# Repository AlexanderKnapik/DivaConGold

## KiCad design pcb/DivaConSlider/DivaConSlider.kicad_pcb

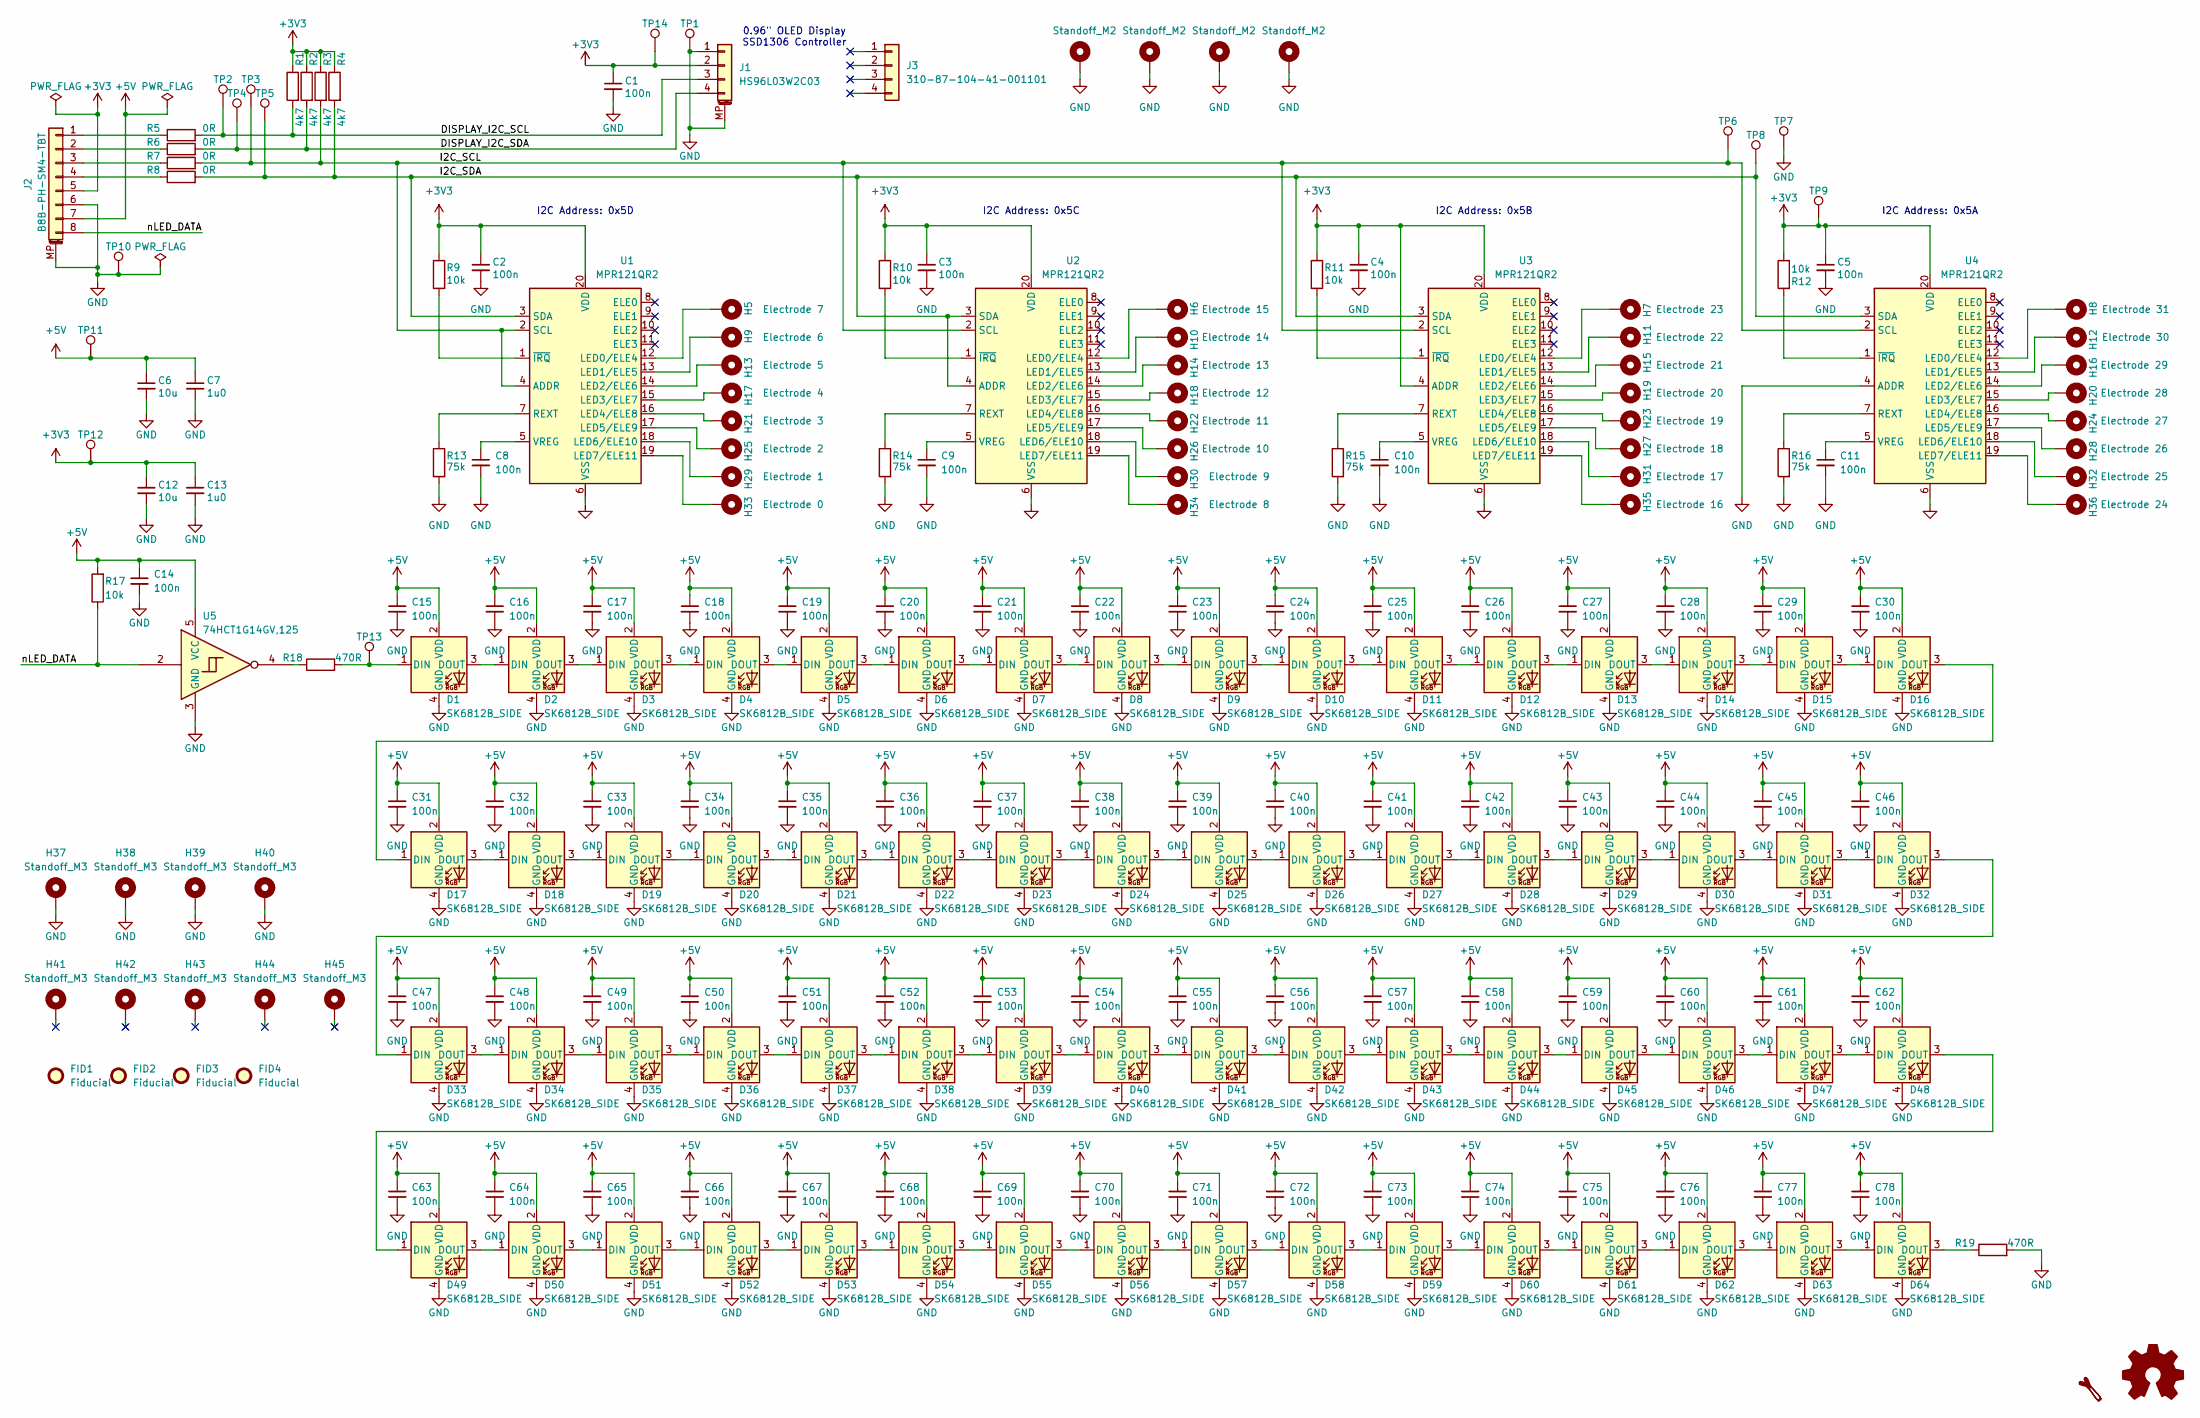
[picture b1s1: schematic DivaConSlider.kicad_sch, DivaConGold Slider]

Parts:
C1, C2, C3, C4, C5, C8, C9, C10, C11, C14, C15, C16, C17, C18, C19, C20, C21, C22, C23, C24, C25, C26, C27, C28, C29, C30, C31, C32, C33, C34, C35, C36, C37, C38, C39, C40, C41, C42, C43, C44, C45, C46, C47, C48, C49, C50, C51, C52, C53, C54, C55, C56, C57, C58, C59, C60, C61, C62, C63, C64, C65, C66, C67, C68, C69, C70, C71, C72, C73, C74, C75, C76, C77, C78: 100n; C_0603_1608Metric; Voltage 50V; PartNumber CL10B104KB8NNNC
C6, C12: 10u; C_0805_2012Metric; Voltage 16V; PartNumber CL21B106KOQNNNE
C7, C13: 1u0; C_0603_1608Metric; Voltage 16V; PartNumber CL10B105KO8NNNC
D1, D2, D3, D4, D5, D6, D7, D8, D9, D10, D11, D12, D13, D14, D15, D16, D17, D18, D19, D20, D21, D22, D23, D24, D25, D26, D27, D28, D29, D30, D31, D32, D33, D34, D35, D36, D37, D38, D39, D40, D41, D42, D43, D44, D45, D46, D47, D48, D49, D50, D51, D52, D53, D54, D55, D56, D57, D58, D59, D60, D61, D62, D63, D64: SK6812B_SIDE; LED_SK6812B_SIDE; PartNumber SK6812SIDE-A
FID1, FID2, FID3, FID4: Fiducial; Fiducial_0.5mm_Mask1.5mm
H1, H2, H3, H4: Standoff_M2; MountingHole_2.2mm_M2_Pad
H5: Electrode 7; Touchpad_15mmx42mm
H6: Electrode 15; Touchpad_15mmx42mm
H7: Electrode 23; Touchpad_15mmx42mm
H8: Electrode 31; Touchpad_15mmx42mm
H9: Electrode 6; Touchpad_15mmx42mm
H10: Electrode 14; Touchpad_15mmx42mm
H11: Electrode 22; Touchpad_15mmx42mm
H12: Electrode 30; Touchpad_15mmx42mm
H13: Electrode 5; Touchpad_15mmx42mm
H14: Electrode 13; Touchpad_15mmx42mm
H15: Electrode 21; Touchpad_15mmx42mm
H16: Electrode 29; Touchpad_15mmx42mm
H17: Electrode 4; Touchpad_15mmx42mm
H18: Electrode 12; Touchpad_15mmx42mm
H19: Electrode 20; Touchpad_15mmx42mm
H20: Electrode 28; Touchpad_15mmx42mm
H21: Electrode 3; Touchpad_15mmx42mm
H22: Electrode 11; Touchpad_15mmx42mm
H23: Electrode 19; Touchpad_15mmx42mm
H24: Electrode 27; Touchpad_15mmx42mm
H25: Electrode 2; Touchpad_15mmx42mm
H26: Electrode 10; Touchpad_15mmx42mm
H27: Electrode 18; Touchpad_15mmx42mm
H28: Electrode 26; Touchpad_15mmx42mm
H29: Electrode 1; Touchpad_15mmx42mm
H30: Electrode 9; Touchpad_15mmx42mm
H31: Electrode 17; Touchpad_15mmx42mm
H32: Electrode 25; Touchpad_15mmx42mm
H33: Electrode 0; Touchpad_15mmx42mm
H34: Electrode 8; Touchpad_15mmx42mm
H35: Electrode 16; Touchpad_15mmx42mm
H36: Electrode 24; Touchpad_15mmx42mm
H37, H38, H39, H40: Standoff_M3; MountingHole_3.2mm_M3_Pad_Via
H41, H42, H43, H44, H45: Standoff_M3; MountingHole_3.2mm_M3_Pad
J1: HS96L03W2C03; Hansheng_HS96L03W2C03; PartNumber HS96L03W2C03
J2: B8B-PH-SM4-TBT; JST_PH_B8B-PH-SM4-TB_1x08-1MP_P2.00mm_Vertical; PartNumber B8B-PH-SM4-TBT
J3: 310-87-104-41-001101; PinHeader_1x04_P2.54mm_Vertical; PartNumber 310-87-104-41-001101
R1, R2, R3, R4: 4k7; R_0603_1608Metric; PartNumber RMCF0603FT4K70
R5, R6, R7, R8: 0R; R_0603_1608Metric; PartNumber RMCF0603ZT0R00
R9, R10, R11, R12, R17: 10k; R_0603_1608Metric; PartNumber RMCF0603FT10K0
R13, R14, R15, R16: 75k; R_0603_1608Metric; PartNumber RMCF0603FT75K0
R18: 470R; R_0603_1608Metric; PartNumber RMCF0603FT470R
R19: 470R; R_0603_1608Metric
SYM1: Logo_Open_Hardware_Small; OSHW-Logo_5.7x6mm_SilkScreen
SYM2: Leek; Leek-Logo_6.3mm_Silkscreen
TP1, TP2, TP3, TP4, TP5, TP6, TP7, TP8, TP9, TP10, TP11, TP12, TP13, TP14: TestPoint; TestPoint_Pad_D1.5mm
U1, U2, U3, U4: MPR121QR2; UQFN-20_3x3mm_P0.4mm; PartNumber MPR121QR2
U5: 74HCT1G14GV,125; SC-74A-5_1.55x2.9mm_P0.95mm; PartNumber 74HCT1G14GV,125

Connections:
+3V3: C1.1, C2.1, C3.1, C4.1, C5.1, C12.1, C13.1, J1.2, J2.5, R1.1, R2.1, R3.1, R4.1, R9.1, R10.1, R11.1, R12.2, TP9.1, TP12.1, TP14.1, U1.20 (VDD), U2.20 (VDD), U3.4 (ADDR), U3.20 (VDD), U4.20 (VDD)
+5V: C6.1, C7.1, C14.1, C15.1, C16.1, C17.1, C18.1, C19.1, C20.1, C21.1, C22.1, C23.1, C24.1, C25.1, C26.1, C27.1, C28.1, C29.1, C30.1, C31.1, C32.1, C33.1, C34.1, C35.1, C36.1, C37.1, C38.1, C39.1, C40.1, C41.1, C42.1, C43.1, C44.1, C45.1, C46.1, C47.1, C48.1, C49.1, C50.1, C51.1, C52.1, C53.1, C54.1, C55.1, C56.1, C57.1, C58.1, C59.1, C60.1, C61.1, C62.1, C63.1, C64.1, C65.1, C66.1, C67.1, C68.1, C69.1, C70.1, C71.1, C72.1, C73.1, C74.1, C75.1, C76.1, C77.1, C78.1, D1.2 (VDD), D2.2 (VDD), D3.2 (VDD), D4.2 (VDD), D5.2 (VDD), D6.2 (VDD), D7.2 (VDD), D8.2 (VDD), D9.2 (VDD), D10.2 (VDD), D11.2 (VDD), D12.2 (VDD), D13.2 (VDD), D14.2 (VDD), D15.2 (VDD), D16.2 (VDD), D17.2 (VDD), D18.2 (VDD), D19.2 (VDD), D20.2 (VDD), D21.2 (VDD), D22.2 (VDD), D23.2 (VDD), D24.2 (VDD), D25.2 (VDD), D26.2 (VDD), D27.2 (VDD), D28.2 (VDD), D29.2 (VDD), D30.2 (VDD), D31.2 (VDD), D32.2 (VDD), D33.2 (VDD), D34.2 (VDD), D35.2 (VDD), D36.2 (VDD), D37.2 (VDD), D38.2 (VDD), D39.2 (VDD), D40.2 (VDD), D41.2 (VDD), D42.2 (VDD), D43.2 (VDD), D44.2 (VDD), D45.2 (VDD), D46.2 (VDD), D47.2 (VDD), D48.2 (VDD), D49.2 (VDD), D50.2 (VDD), D51.2 (VDD), D52.2 (VDD), D53.2 (VDD), D54.2 (VDD), D55.2 (VDD), D56.2 (VDD), D57.2 (VDD), D58.2 (VDD), D59.2 (VDD), D60.2 (VDD), D61.2 (VDD), D62.2 (VDD), D63.2 (VDD), D64.2 (VDD), J2.7, R17.2, TP11.1, U5.5 (VCC)
/DISPLAY_I2C_SCL: J1.3, R1.2, R5.2, TP2.1
/DISPLAY_I2C_SDA: J1.4, R2.2, R6.2, TP4.1
/I2C_SCL: R3.2, R7.2, TP3.1, TP6.1, U1.2 (SCL), U1.4 (ADDR), U2.2 (SCL), U3.2 (SCL), U4.2 (SCL)
/I2C_SDA: R4.2, R8.2, TP5.1, TP8.1, U1.3 (SDA), U2.3 (SDA), U2.4 (ADDR), U3.3 (SDA), U4.3 (SDA)
/nLED_DATA: J2.8, R17.1, U5.2
GND: C1.2, C2.2, C3.2, C4.2, C5.2, C6.2, C7.2, C8.2, C9.2, C10.2, C11.2, C12.2, C13.2, C14.2, C15.2, C16.2, C17.2, C18.2, C19.2, C20.2, C21.2, C22.2, C23.2, C24.2, C25.2, C26.2, C27.2, C28.2, C29.2, C30.2, C31.2, C32.2, C33.2, C34.2, C35.2, C36.2, C37.2, C38.2, C39.2, C40.2, C41.2, C42.2, C43.2, C44.2, C45.2, C46.2, C47.2, C48.2, C49.2, C50.2, C51.2, C52.2, C53.2, C54.2, C55.2, C56.2, C57.2, C58.2, C59.2, C60.2, C61.2, C62.2, C63.2, C64.2, C65.2, C66.2, C67.2, C68.2, C69.2, C70.2, C71.2, C72.2, C73.2, C74.2, C75.2, C76.2, C77.2, C78.2, D1.4 (GND), D2.4 (GND), D3.4 (GND), D4.4 (GND), D5.4 (GND), D6.4 (GND), D7.4 (GND), D8.4 (GND), D9.4 (GND), D10.4 (GND), D11.4 (GND), D12.4 (GND), D13.4 (GND), D14.4 (GND), D15.4 (GND), D16.4 (GND), D17.4 (GND), D18.4 (GND), D19.4 (GND), D20.4 (GND), D21.4 (GND), D22.4 (GND), D23.4 (GND), D24.4 (GND), D25.4 (GND), D26.4 (GND), D27.4 (GND), D28.4 (GND), D29.4 (GND), D30.4 (GND), D31.4 (GND), D32.4 (GND), D33.4 (GND), D34.4 (GND), D35.4 (GND), D36.4 (GND), D37.4 (GND), D38.4 (GND), D39.4 (GND), D40.4 (GND), D41.4 (GND), D42.4 (GND), D43.4 (GND), D44.4 (GND), D45.4 (GND), D46.4 (GND), D47.4 (GND), D48.4 (GND), D49.4 (GND), D50.4 (GND), D51.4 (GND), D52.4 (GND), D53.4 (GND), D54.4 (GND), D55.4 (GND), D56.4 (GND), D57.4 (GND), D58.4 (GND), D59.4 (GND), D60.4 (GND), D61.4 (GND), D62.4 (GND), D63.4 (GND), D64.4 (GND), H1.1, H2.1, H3.1, H4.1, H37.1, H38.1, H39.1, H40.1, J1.1, J1.MP (MountPin), J2.6, J2.MP (MountPin), R13.2, R14.2, R15.2, R16.2, R19.2, TP1.1, TP7.1, TP10.1, U1.6 (VSS), U2.6 (VSS), U3.6 (VSS), U4.4 (ADDR), U4.6 (VSS), U5.3 (GND)
unnamed: D1.1 (DIN), R18.2, TP13.1
unnamed: D1.3 (DOUT), D2.1 (DIN)
unnamed: D2.3 (DOUT), D3.1 (DIN)
unnamed: D3.3 (DOUT), D4.1 (DIN)
unnamed: D4.3 (DOUT), D5.1 (DIN)
unnamed: D5.3 (DOUT), D6.1 (DIN)
unnamed: D6.3 (DOUT), D7.1 (DIN)
unnamed: D7.3 (DOUT), D8.1 (DIN)
unnamed: D8.3 (DOUT), D9.1 (DIN)
unnamed: D9.3 (DOUT), D10.1 (DIN)
unnamed: D10.3 (DOUT), D11.1 (DIN)
unnamed: D11.3 (DOUT), D12.1 (DIN)
unnamed: D12.3 (DOUT), D13.1 (DIN)
unnamed: D13.3 (DOUT), D14.1 (DIN)
unnamed: D14.3 (DOUT), D15.1 (DIN)
unnamed: D15.3 (DOUT), D16.1 (DIN)
unnamed: D16.3 (DOUT), D17.1 (DIN)
unnamed: D17.3 (DOUT), D18.1 (DIN)
unnamed: D18.3 (DOUT), D19.1 (DIN)
unnamed: D19.3 (DOUT), D20.1 (DIN)
unnamed: D20.3 (DOUT), D21.1 (DIN)
unnamed: D21.3 (DOUT), D22.1 (DIN)
unnamed: D22.3 (DOUT), D23.1 (DIN)
unnamed: D23.3 (DOUT), D24.1 (DIN)
unnamed: D24.3 (DOUT), D25.1 (DIN)
unnamed: D25.3 (DOUT), D26.1 (DIN)
unnamed: D26.3 (DOUT), D27.1 (DIN)
unnamed: D27.3 (DOUT), D28.1 (DIN)
unnamed: D28.3 (DOUT), D29.1 (DIN)
unnamed: D29.3 (DOUT), D30.1 (DIN)
unnamed: D30.3 (DOUT), D31.1 (DIN)
unnamed: D31.3 (DOUT), D32.1 (DIN)
unnamed: D32.3 (DOUT), D33.1 (DIN)
unnamed: D33.3 (DOUT), D34.1 (DIN)
unnamed: D34.3 (DOUT), D35.1 (DIN)
unnamed: D35.3 (DOUT), D36.1 (DIN)
unnamed: D36.3 (DOUT), D37.1 (DIN)
unnamed: D37.3 (DOUT), D38.1 (DIN)
unnamed: D38.3 (DOUT), D39.1 (DIN)
unnamed: D39.3 (DOUT), D40.1 (DIN)
unnamed: D40.3 (DOUT), D41.1 (DIN)
unnamed: D41.3 (DOUT), D42.1 (DIN)
unnamed: D42.3 (DOUT), D43.1 (DIN)
unnamed: D43.3 (DOUT), D44.1 (DIN)
unnamed: D44.3 (DOUT), D45.1 (DIN)
unnamed: D45.3 (DOUT), D46.1 (DIN)
unnamed: D46.3 (DOUT), D47.1 (DIN)
unnamed: D47.3 (DOUT), D48.1 (DIN)
unnamed: D48.3 (DOUT), D49.1 (DIN)
unnamed: D49.3 (DOUT), D50.1 (DIN)
unnamed: D50.3 (DOUT), D51.1 (DIN)
unnamed: D51.3 (DOUT), D52.1 (DIN)
unnamed: D52.3 (DOUT), D53.1 (DIN)
unnamed: D53.3 (DOUT), D54.1 (DIN)
unnamed: D54.3 (DOUT), D55.1 (DIN)
unnamed: D55.3 (DOUT), D56.1 (DIN)
unnamed: D56.3 (DOUT), D57.1 (DIN)
unnamed: D57.3 (DOUT), D58.1 (DIN)
unnamed: D58.3 (DOUT), D59.1 (DIN)
unnamed: D59.3 (DOUT), D60.1 (DIN)
unnamed: D60.3 (DOUT), D61.1 (DIN)
unnamed: D61.3 (DOUT), D62.1 (DIN)
unnamed: D62.3 (DOUT), D63.1 (DIN)
unnamed: D63.3 (DOUT), D64.1 (DIN)
unnamed: D64.3 (DOUT), R19.1
unnamed: J2.1, R5.1
unnamed: J2.2, R6.1
unnamed: J2.3, R7.1
unnamed: J2.4, R8.1
unnamed: R18.1, U5.4
unnamed: H5.1, U1.12 (LED0/ELE4)
unnamed: H9.1, U1.13 (LED1/ELE5)
unnamed: H13.1, U1.14 (LED2/ELE6)
unnamed: H17.1, U1.15 (LED3/ELE7)
unnamed: H21.1, U1.16 (LED4/ELE8)
unnamed: H25.1, U1.17 (LED5/ELE9)
unnamed: H29.1, U1.18 (LED6/ELE10)
unnamed: H33.1, U1.19 (LED7/ELE11)
unnamed: R13.1, U1.7 (REXT)
unnamed: C8.1, U1.5 (VREG)
unnamed: R9.2, U1.1 (~IRQ)
unnamed: H6.1, U2.12 (LED0/ELE4)
unnamed: H10.1, U2.13 (LED1/ELE5)
unnamed: H14.1, U2.14 (LED2/ELE6)
unnamed: H18.1, U2.15 (LED3/ELE7)
unnamed: H22.1, U2.16 (LED4/ELE8)
unnamed: H26.1, U2.17 (LED5/ELE9)
unnamed: H30.1, U2.18 (LED6/ELE10)
unnamed: H34.1, U2.19 (LED7/ELE11)
unnamed: R14.1, U2.7 (REXT)
unnamed: C9.1, U2.5 (VREG)
unnamed: R10.2, U2.1 (~IRQ)
unnamed: H7.1, U3.12 (LED0/ELE4)
unnamed: H11.1, U3.13 (LED1/ELE5)
unnamed: H15.1, U3.14 (LED2/ELE6)
unnamed: H19.1, U3.15 (LED3/ELE7)
unnamed: H23.1, U3.16 (LED4/ELE8)
unnamed: H27.1, U3.17 (LED5/ELE9)
unnamed: H31.1, U3.18 (LED6/ELE10)
unnamed: H35.1, U3.19 (LED7/ELE11)
unnamed: R15.1, U3.7 (REXT)
unnamed: C10.1, U3.5 (VREG)
unnamed: R11.2, U3.1 (~IRQ)
unnamed: H8.1, U4.12 (LED0/ELE4)
unnamed: H12.1, U4.13 (LED1/ELE5)
unnamed: H16.1, U4.14 (LED2/ELE6)
unnamed: H20.1, U4.15 (LED3/ELE7)
unnamed: H24.1, U4.16 (LED4/ELE8)
unnamed: H28.1, U4.17 (LED5/ELE9)
unnamed: H32.1, U4.18 (LED6/ELE10)
unnamed: H36.1, U4.19 (LED7/ELE11)
unnamed: R16.1, U4.7 (REXT)
unnamed: C11.1, U4.5 (VREG)
unnamed: R12.1, U4.1 (~IRQ)

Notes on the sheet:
I2C Address: 0x5B
I2C Address: 0x5C
I2C Address: 0x5D
I2C Address: 0x5A
0.96" OLED Display SSD1306 Controller

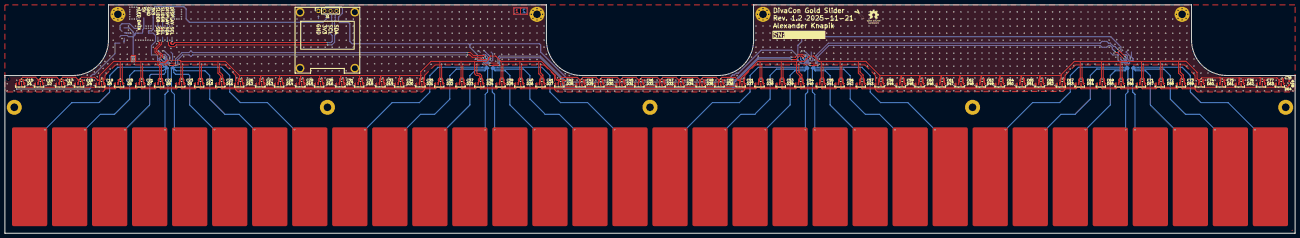
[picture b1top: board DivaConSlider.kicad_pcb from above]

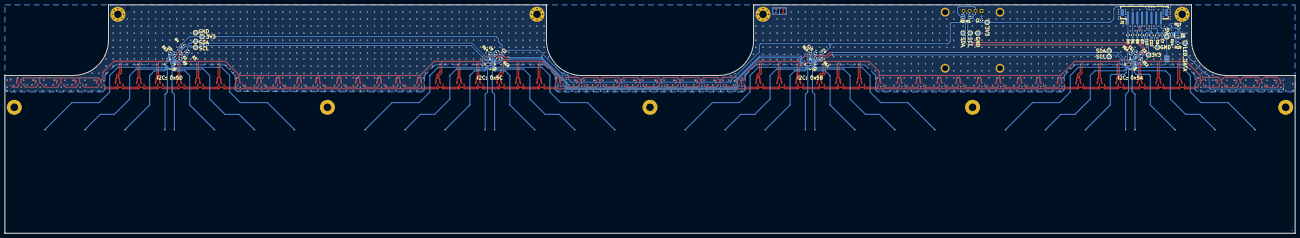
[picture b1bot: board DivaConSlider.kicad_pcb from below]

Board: 2 copper layers, 548.0 x 97.0 mm, 229 parts (54 on the bottom side), 122 nets.

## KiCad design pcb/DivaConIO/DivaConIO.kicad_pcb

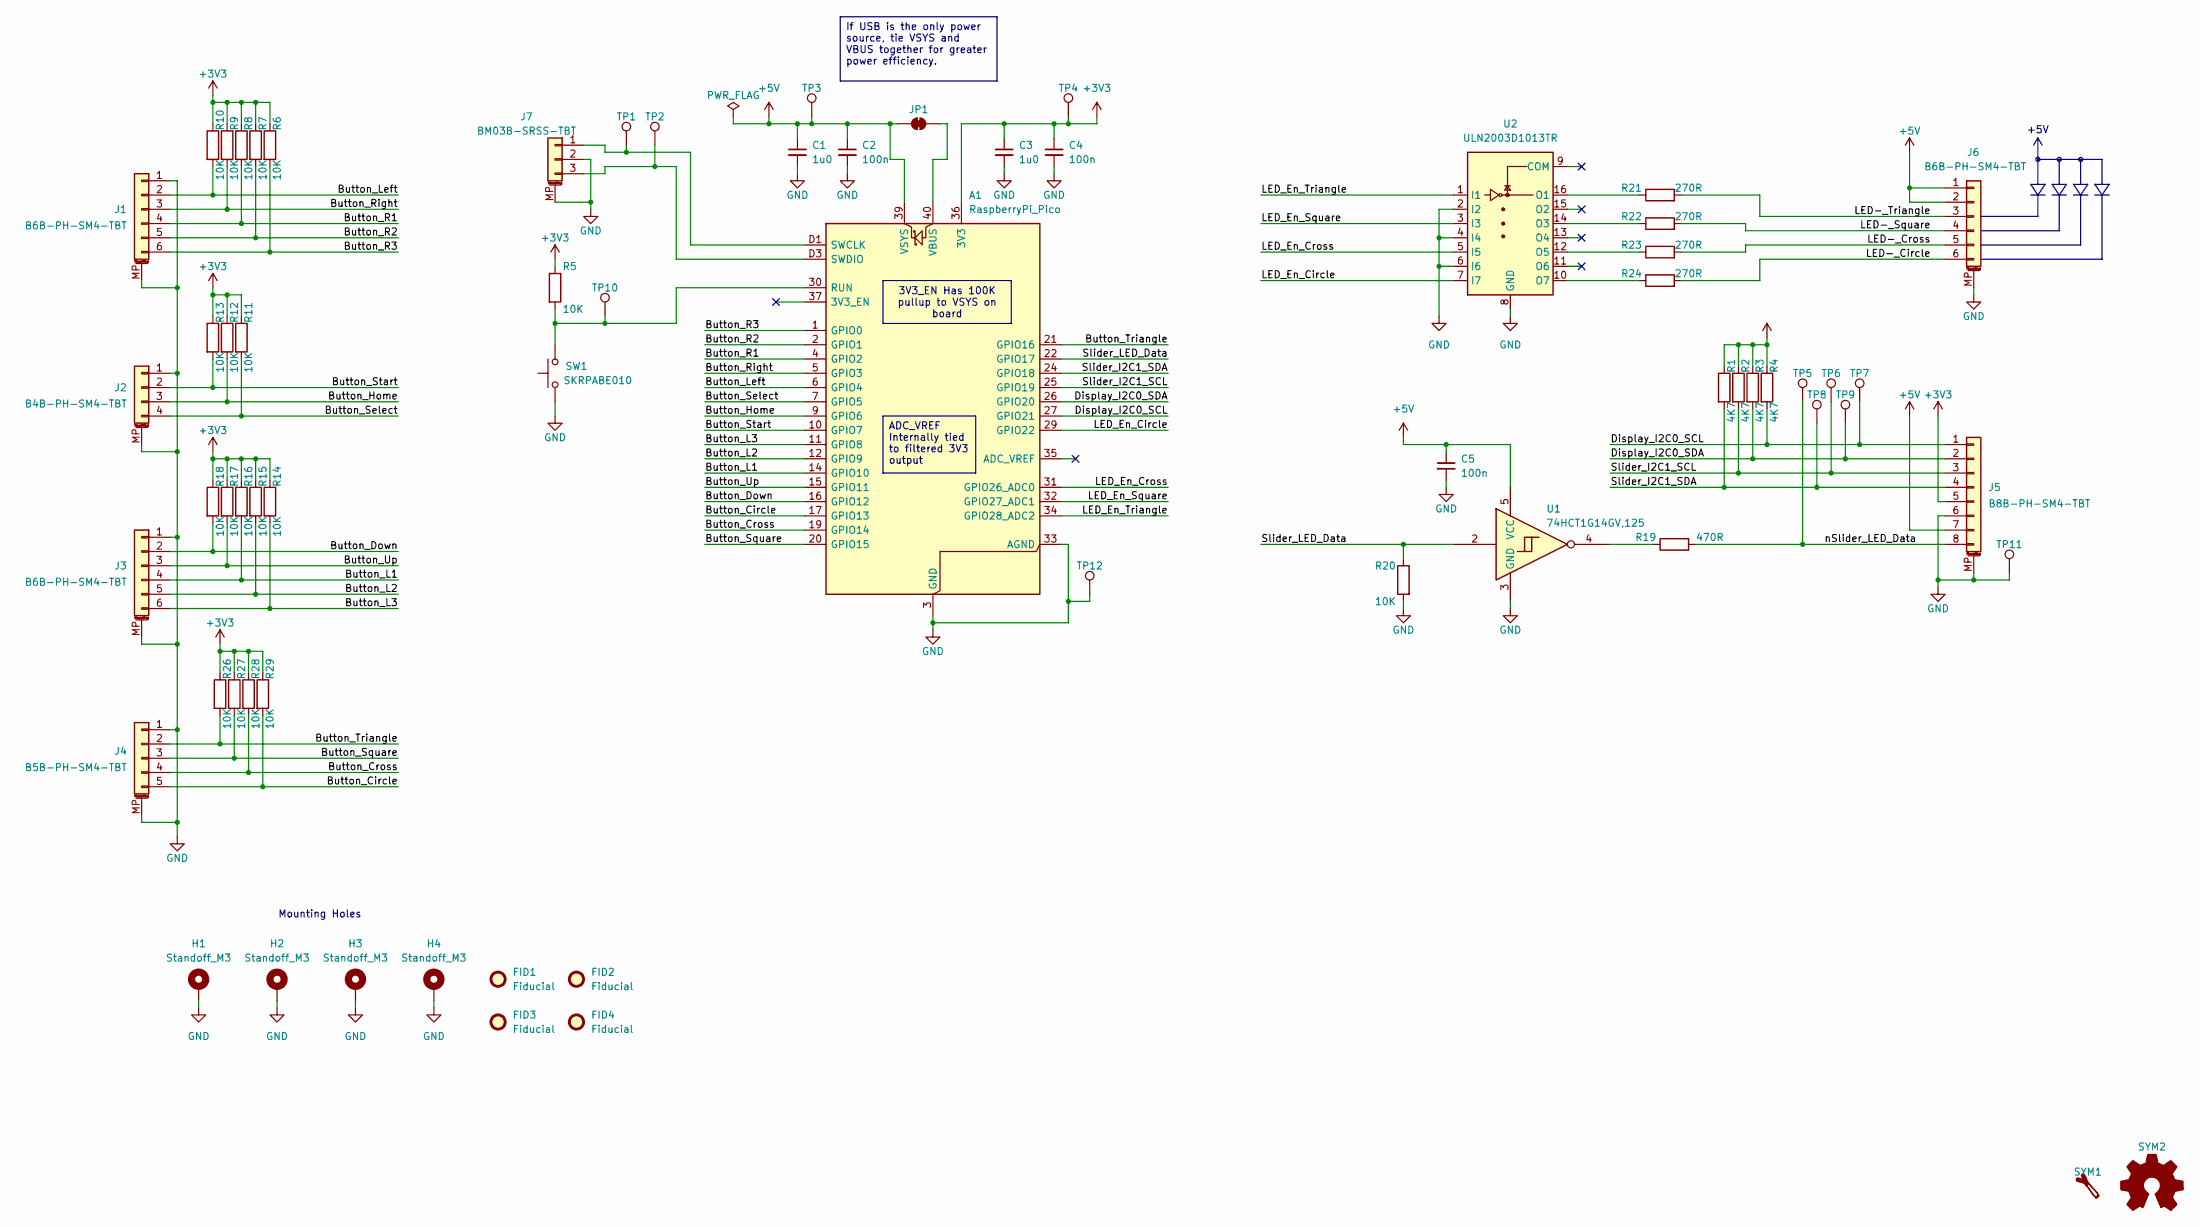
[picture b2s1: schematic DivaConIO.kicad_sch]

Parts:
A1: RaspberryPi_Pico; RaspberryPi_Pico_SMD_HandSolder; PartNumber SC0915
C1, C3: 1u0; C_0603_1608Metric; Voltage 16V; PartNumber CL10B105KO8NNNC
C2, C4, C5: 100n; C_0603_1608Metric; Voltage 50V; PartNumber CL10B104KB8NNNC
FID1, FID2, FID3, FID4: Fiducial; Fiducial_0.5mm_Mask1.5mm
H1, H2, H3, H4: Standoff_M3; MountingHole_3.2mm_M3_Pad_Via
J1, J3, J6: B6B-PH-SM4-TBT; JST_PH_B6B-PH-SM4-TB_1x06-1MP_P2.00mm_Vertical; PartNumber B6B-PH-SM4-TBT
J2: B4B-PH-SM4-TBT; JST_PH_B4B-PH-SM4-TB_1x04-1MP_P2.00mm_Vertical; PartNumber B4B-PH-SM4-TBT
J4: B5B-PH-SM4-TBT; JST_PH_B5B-PH-SM4-TB_1x05-1MP_P2.00mm_Vertical; PartNumber B5B-PH-SM4-TBT
J5: B8B-PH-SM4-TBT; JST_PH_B8B-PH-SM4-TB_1x08-1MP_P2.00mm_Vertical; PartNumber B8B-PH-SM4-TBT
J7: BM03B-SRSS-TBT; JST_SH_BM03B-SRSS-TB_1x03-1MP_P1.00mm_Vertical; PartNumber BM03B-SRSS-TBT
JP1: SolderJumper_2_Bridged; SolderJumper-2_P1.3mm_Bridged_RoundedPad1.0x1.5mm
R1, R2, R3, R4: 4K7; R_0603_1608Metric; PartNumber RMCF0603FT4K70
R5, R6, R7, R8, R9, R10, R11, R12, R13, R14, R15, R16, R17, R18, R20, R26, R27, R28, R29: 10K; R_0603_1608Metric; PartNumber RMCF0603FT10K0
R19: 470R; R_0603_1608Metric; PartNumber RMCF0603FT470R
R21, R22, R23, R24: 270R; R_1206_3216Metric; PartNumber RMCF1206JT270R
SW1: SKRPABE010; SW_Push_SPST_NO_Alps_SKRP; PartNumber SKRPABE010
SYM1: Leek; Leek-Logo_6.3mm_Silkscreen
SYM2: Logo_Open_Hardware_Small; OSHW-Logo2_7.3x6mm_SilkScreen
TP1, TP2, TP3, TP4, TP5, TP6, TP7, TP8, TP9, TP10, TP11, TP12: TestPoint; TestPoint_Pad_D2.0mm
U1: 74HCT1G14GV,125; SC-74A-5_1.55x2.9mm_P0.95mm; PartNumber 74HCT1G14GV,125
U2: ULN2003D1013TR; SOIC-16_3.9x9.9mm_P1.27mm; PartNumber ULN2003D1013TR

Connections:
+3V3: A1.36 (3V3), C3.1, C4.1, J5.5, R1.1, R2.1, R3.1, R4.1, R5.1, R6.1, R7.1, R8.1, R9.1, R10.1, R11.1, R12.1, R13.1, R14.1, R15.1, R16.1, R17.1, R18.1, R26.1, R27.1, R28.1, R29.1, TP4.1
+5V: A1.39 (VSYS), C1.1, C2.1, C5.1, J5.7, J6.1, J6.2, JP1.1 (A), TP3.1, U1.5 (VCC)
/Button_Circle: A1.17 (GPIO13), J4.5, R29.2
/Button_Cross: A1.19 (GPIO14), J4.4, R28.2
/Button_Down: A1.16 (GPIO12), J3.2, R18.2
/Button_Home: A1.9 (GPIO6), J2.3, R12.2
/Button_L1: A1.14 (GPIO10), J3.4, R16.2
/Button_L2: A1.12 (GPIO9), J3.5, R15.2
/Button_L3: A1.11 (GPIO8), J3.6, R14.2
/Button_Left: A1.6 (GPIO4), J1.2, R10.2
/Button_R1: A1.4 (GPIO2), J1.4, R8.2
/Button_R2: A1.2 (GPIO1), J1.5, R7.2
/Button_R3: A1.1 (GPIO0), J1.6, R6.2
/Button_Right: A1.5 (GPIO3), J1.3, R9.2
/Button_Select: A1.7 (GPIO5), J2.4, R11.2
/Button_Square: A1.20 (GPIO15), J4.3, R27.2
/Button_Start: A1.10 (GPIO7), J2.2, R13.2
/Button_Triangle: A1.21 (GPIO16), J4.2, R26.2
/Button_Up: A1.15 (GPIO11), J3.3, R17.2
/Display_I2C0_SCL: A1.27 (GPIO21), J5.1, R4.2, TP7.1
/Display_I2C0_SDA: A1.26 (GPIO20), J5.2, R3.2, TP9.1
/LED-_Circle: J6.6, R24.2
/LED-_Cross: J6.5, R23.2
/LED-_Square: J6.4, R22.2
/LED-_Triangle: J6.3, R21.2
/LED_En_Circle: A1.29 (GPIO22), U2.7 (I7)
/LED_En_Cross: A1.31 (GPIO26_ADC0), U2.5 (I5)
/LED_En_Square: A1.32 (GPIO27_ADC1), U2.3 (I3)
/LED_En_Triangle: A1.34 (GPIO28_ADC2), U2.1 (I1)
/Slider_I2C1_SCL: A1.25 (GPIO19), J5.3, R2.2, TP6.1
/Slider_I2C1_SDA: A1.24 (GPIO18), J5.4, R1.2, TP8.1
/Slider_LED_Data: A1.22 (GPIO17), R20.1, U1.2
/nSlider_LED_Data: J5.8, R19.2, TP5.1
GND: A1.3 (GND), A1.8 (GND), A1.13 (GND), A1.18 (GND), A1.23 (GND), A1.28 (GND), A1.33 (AGND), A1.38 (GND), A1.D2 (GND), C1.2, C2.2, C3.2, C4.2, C5.2, H1.1, H2.1, H3.1, H4.1, J1.1, J1.MP (MountPin), J2.1, J2.MP (MountPin), J3.1, J3.MP (MountPin), J4.1, J4.MP (MountPin), J5.6, J5.MP (MountPin), J6.MP (MountPin), J7.2, J7.MP (MountPin), R20.2, SW1.1, TP11.1, TP12.1, U1.3 (GND), U2.2 (I2), U2.4 (I4), U2.6 (I6), U2.8 (GND)
unnamed: A1.30 (RUN), R5.2, SW1.2, TP10.1
unnamed: A1.D1 (SWCLK), J7.1, TP1.1
unnamed: A1.D3 (SWDIO), J7.3, TP2.1
unnamed: A1.40 (VBUS), JP1.2 (B)
unnamed: R19.1, U1.4
unnamed: R21.1, U2.16 (O1)
unnamed: R22.1, U2.14 (O3)
unnamed: R23.1, U2.12 (O5)
unnamed: R24.1, U2.10 (O7)

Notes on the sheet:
Mounting Holes
+5V
ADC_VREF Internally tied to filtered 3V3 output
If USB is the only power source, tie VSYS and VBUS together for greater power efficiency.
3V3_EN Has 100K pullup to VSYS on board

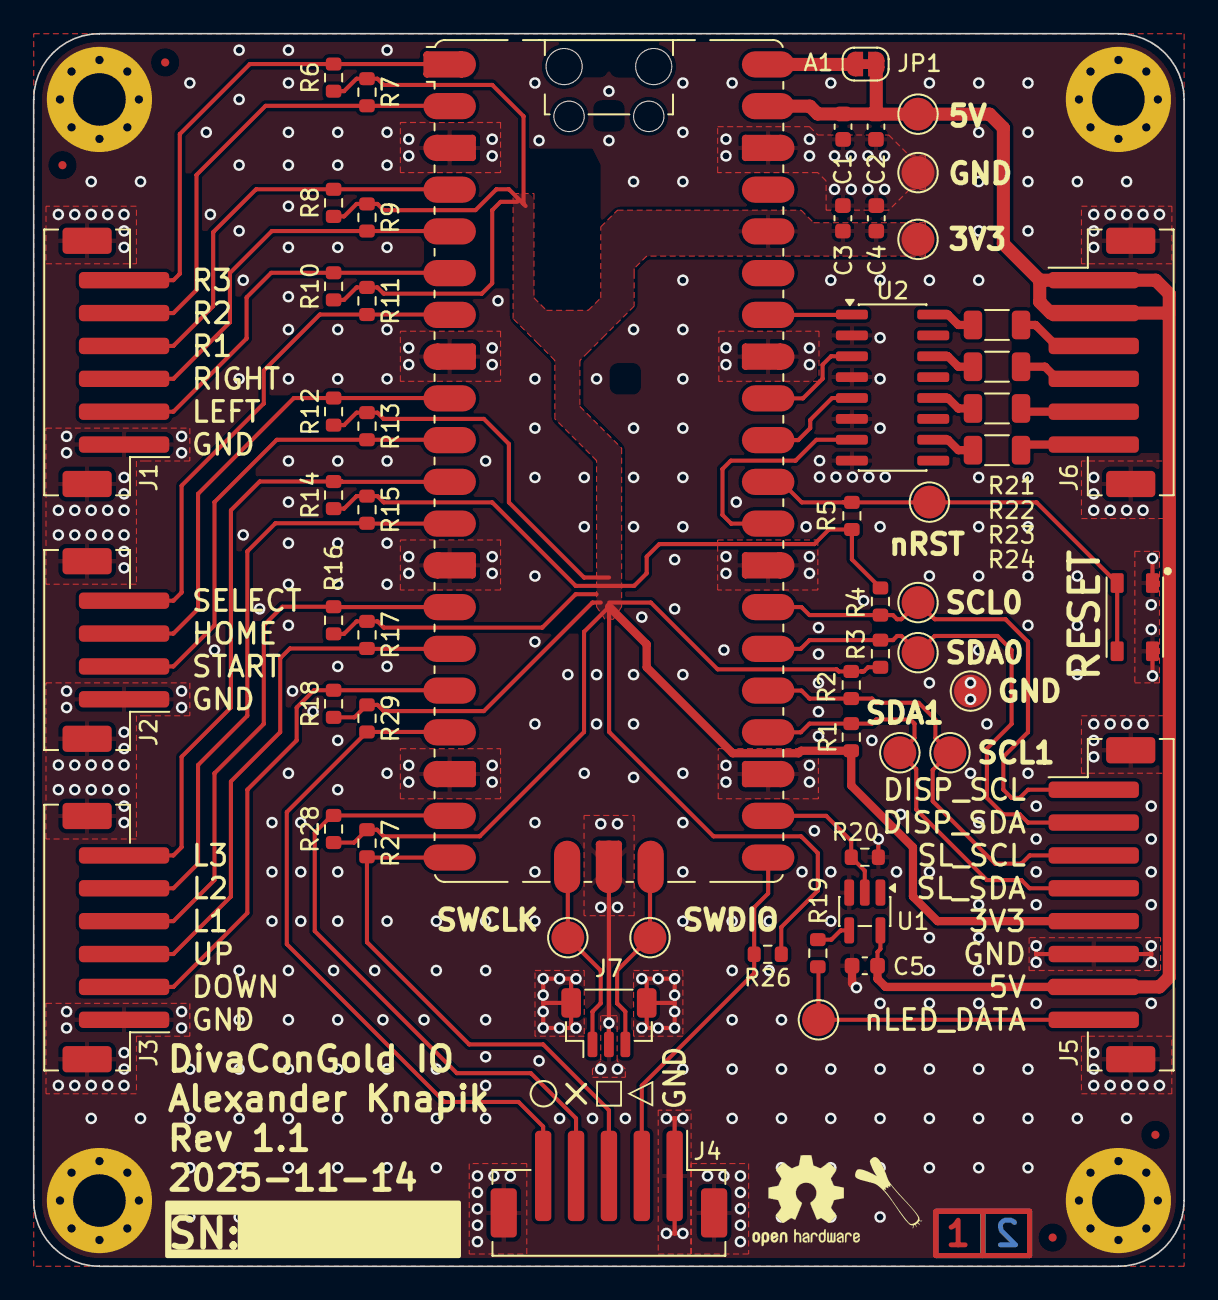
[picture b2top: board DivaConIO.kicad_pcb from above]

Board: 2 copper layers, 70.0 x 75.0 mm, 67 parts (0 on the bottom side), 43 nets.

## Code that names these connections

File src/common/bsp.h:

/*****************************************************************************/
/*                Board Support Package Hardware Configuration               */
/*****************************************************************************/
#ifndef BSP_H_
#define BSP_H_

#ifdef __cplusplus
extern "C" {
#endif


#define MPR121_I2C_TIMEOUT_MS (100U)

/* 0 is active low, 1 is active high */
#define BUTTON_ACTIVE_LEVEL (0U)
#define BUTTON_LED_ACTIVE_LEVEL (1U)

#define I2C_SLEW_RATE (GPIO_SLEW_RATE_HIGH)
#define BUTTON_R1_Pin (2U)
#define BUTTON_R2_Pin (1U)
#define BUTTON_R3_Pin (0U)

#define BUTTON_L1_Pin (10U)
#define BUTTON_L2_Pin (9U)
#define BUTTON_L3_Pin (8U)

#define BUTTON_UP_Pin (11U)
#define BUTTON_DOWN_Pin (12U)
#define BUTTON_LEFT_Pin (4U)
#define BUTTON_RIGHT_Pin (3U)

#define BUTTON_SELECT_Pin (5U)
#define BUTTON_HOME_Pin (6U)
#define BUTTON_START_Pin (7U)

#define BUTTON_CIRCLE_Pin (13U)
#define BUTTON_CROSS_Pin (14U)
#define BUTTON_SQUARE_Pin (15U)
#define BUTTON_TRIANGLE_Pin (16U)
#define SLIDER_LED_DATA_Pin (17U)

#define LED_CIRCLE_Pin (22U)
#define LED_CROSS_Pin (26U)
#define LED_SQUARE_Pin (27U)
#define LED_TRIANGLE_Pin (28U)

#define SLIDER_I2C1_SDA_Pin (18U)
#define SLIDER_I2C1_SCL_Pin (19U)
#define DISPLAY_I2C0_SDA_Pin (20U)
#define DISPLAY_I2C0_SCL_Pin (21U)

#ifdef __cplusplus
}
#endif

#endif // BSP_H_

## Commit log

2025-09-20 relaid out IO board
2025-09-20 documenting wiring diagram
2025-09-21 refactoring cmake build
2025-09-21 placing both I2C buses on the same connector
2025-09-26 Switch to c++20
2025-09-26 clang-tidy: fix include guards
2025-09-28 clang-tidy: modernize
2025-09-28 clang-tidy: fix clang diagnostics
2025-09-28 clang-tidy: misc
2025-09-28 ws2812_pio: properly latch led data
2025-09-28 refactor: remove static variables in members
2025-09-28 clang-tidy libs
2025-09-28 clang-tidy: cppcoreguidelines
2025-09-28 Refactor InputState
2025-09-28 clang-tidy: bugprone
2025-09-28 clang-tidy: performance and readability
2025-11-14 update revision 1.0 wiring diagram
2025-11-14 revision 1.1 pcb schematics and layout
2025-11-14 revision 1.0 pcb schematics and layout
2025-11-14 generate revision 1.0 gerber files
2025-11-14 Update and move harness from doc
2025-11-14 Update gerbers to purchased revision
2025-11-14 Update PCBs to purchased revision
    Main edit is using a ULN2003 NPN transistor array over discrete MOSFETs.
    This was chosen because there was limited board space to put in
    pull-down resistors on the board and it was complicating the single
    layer routing. The PCB had to be expanded to 70x75mm anyways to
    accommodate the SOIC ic anyways.
    The schematics of the IO board were also updated to use net labels over
2025-11-14 generate revision 1.1 gerber files
2025-11-14 Move gerbers to pcb project folders
2025-11-14 Combined IO & Slider board PCB stencil project
    Created a solder paste stencil project that has both layers of the
    slider board and the top layer of the IO board on the same layer. This
    saves some cost in getting PCB stencils manufactured.
2025-11-21 Fix slider led_data silkscreen
    Didn't indicate active low on the connector, had just "DATA" for the
    test point, and had a redundant old silk screen label from a removed
    test point location
2025-12-05 Generate slider PCB 3d model
2025-12-05 Initial enclosure design
    Essentially just playing around and trying to figure out how to design
    an enclosure
2025-12-05 Update pin numbering for DivaConGold
2025-12-12 Get project compiling without USB
    Something is wrong with the USB stdio initialisation at the moment which
    is causing a hard fault. Getting to the stage where I can compile and
    run the code before troubleshooting.
2025-12-12 Fix reversed touch slider pins
    Previously, the slider ICs were on the front side of the PCB, but now
    they have moved to the bottom side. This means that the pins that each
    slider connected to the MPR121 is now reversed.
2025-12-12 Delete dead slider code
    No longer using the other ICs, so I'm deleting them from potential
    configurations. This should ideally have been handled via CMake instead.
2026-01-05 Combine src and include folders for libraries
2026-01-05 Combine project src and include folders
    It was getting too confusing to dive into all the include directories,
    so I'll just move them into the same folder as all the rest of the
    source files.
2026-01-05 Cmake target to flash with openocd
2026-01-07 Rewrote code for handling BPM
2026-01-07 Support building unit testing
    Updated the build system to support CMocka in the future.
2026-01-07 Update clang-format
    I didn't like how functions didn't require a K&R break for the braces.
    Also limiting the column limit.
2026-01-07 Rewrite driver for button handling
2026-01-19 Circular buffer for storing slider led animations
2026-01-19 Documenting firmware structure
2026-01-19 Delete old DivaCon2040 code
    It's difficult keeping version controlling two different set of project files
    within the repository, so they will be deleted and brought back as needed.
2026-01-19 Delete divacon_gold CMake target
    No longer necessary at this point. The idea was to be able to unit test
    the system by compiling everything apart from main() as a library to be
    linked against. May be reimplemented again in a future date.
2026-01-19 Rename palette buffer to pattern buffer
    It was rather confusing calling it a palette, when it wasn't a palette
    of all available colours, but rather an animation sequence.
2026-01-20 Common buttons struct header
    Moving the controller buttons struct to a common definition to allow for
    inclusion without including any of the buttons functions.
2026-01-20 Implement various uint util functions
    Functions and macros for getting bits and sizes of uints used through
    the code. Essentially, I used these functions throughout the next
    commits, and I don't want to go through this file constantly checking
    when the certain function was used.
2026-01-20 Versioning the firmware
2026-01-26 Implement millisecond system tick timer
2026-01-26 Print version on startup via USB
    Using USB as a tty port on the PC to send strings and currently printing
    the version on startup. Involves the build system updates in order to
    divert stdio functions to the USB tty.
2026-01-26 Fix incorrectly reporting I2C timeout errors
    Previously, a pico timeout error was getting reported as a E_HARDWARE
    error instead of E_TIMEOUT. The enum errors weren't being converted to
    the correct negative number, so I'm explicitly casting as an enum
    pico_error_codes.
2026-01-26 Wrapper functions for Pico I2C API
    Creating wrapper functions so that multiple devices can share one I2C
    API (despite the SSD1306 library directly including the hardware/i2c.h)
    for configuration without having to include the pico hardware_i2c
    library. Also a nicety in that errors are handled in a common way as
    well as initialising the GPIO pins.
2026-01-26 Remove returned error from i2c_close
    There was no way for this function to fail, plus i2c_deinit() has
    asserts to check for a NULL i2c isntance too, so I'm changing it to a
    void function instead.
2026-01-26 Clean up buttons code
    Various changes mainly related to formatting and error checking. No
    altering the functionality. Also included some comment blocks for header
    files.
2026-01-26 Fix intermittent stuck I2C bus issues on startup
    Initialising the i2c bus multiple times was causing issues with the
    MPR121s and the bus getting stuck with either micro or MPR121s
    constantly holding SDA and SCL low. This was always intended to be a
    singleton, so I've made it check if the I2C peripheral is already
    enabled, and if so, just exit early.
2026-01-26 Move colour struct to common/colour_common.h
2026-01-26 Configure GPIO slew and drive strength
2026-01-26 Rudimentary logging interface
    Currently just using printf to USB stdio functions. Only partially
    implemented at the moment, with no callback function implementation.
2026-01-26 Driver for OLED display to view electrode state
    Currently have implemented a default menu screen that displays the
    currently touched state of the electrodes at the bottom of the screen as
    squares.
2026-01-26 Implement driver for the slider touch sensor
    Higher level driver for the capacitive touch sensors, allowing all four
    touch sensors to be controlled as one device.
2026-01-26 Implement Slider LED animations
    A higher level abstraction to the initial pattern buffer. Handles
    reading and updating the position simultaneously.
    TODO: Brightness control.
2026-01-26 Clean up CMake public library linking
    Making the linked libraries that didn't need to be public, private
    instead.
2026-01-26 Rewrite the MPR121 driver
    Essentially, the only problem previously was that Mpr121.cpp was written
    in C++ (which I'm not familiar with), this meant that I couldn't include
    it directly from a C file. The main differences are is that I've
    extended the configuration during when opening so that it doesn't rely
    on magic numbers, and added error checking. Furthermore, I've added
    function docstrings and labelled all of the register numbers too.
2026-01-26 Basic driver to control the slider LEDs
    Driver that can control the slider LEDs, read from the capacitive touch
    sensor and display the currently touched electrodes as a separate colour
    as an overlay over the animation.
    This is basic driver at the moment, with features such as controlling
    the brightness and settings of the LEDs not yet implemented.
2026-01-26 Fix button counter overflowing when held
2026-01-26 Compile using USB dev_hid_composite example
    Debugging and getting USB working with compiling the tinyusb/pico
    example dev_hid_composite which makes the micro act as multiple types of
    HID devices whenever the BOOTSEL pin is pressed. Using this to just get
    the USB configuration settings in a working baseline state before
    customising.
2026-01-27 USB NKRO keyboard driver
    Rewrote the USB writing keyboard codes to a "NKRO" version that uses
    keycodes as a look-up table instead.
    I've also restructured things a little so that not everything is in the
    one usb.c file, added some rudimentary error checking and cleaning up
    some magic numbers.
2026-01-28 Initial main loop to test hardware
    Currently implemented initialising the display, slider and USB.
    Currently, the program will read buttons, read the touch slider state,
    display it on the display and write the pressed buttons over USB.
    Writing the slider state over USB is not yet implemented.
2026-01-28 Genericise the USB driver
    Genericising the USB driver so that different types of USB modes can be
    instantiated through the one instance, utilising callback functions.
    Currently hardcoding only one USB interface instantiation as the
    tud_descriptor callback functions requires access to a global variable.
2026-01-28 Fix the MSB and LSB util functions
    I hadn't tested these functions previously, and it turns out they
    weren't counting bit positions correctly.
2026-01-28 Report slider state in keyboard USB driver
    The keyboard now decodes the slider state into a keyboard button. The
    USB report function and callback now requires passing in the state to
    the slider.
    TODO: typedef the usb report function callback.
2026-01-28 Read slider directions
    Reading the slider now returns a state struct that has decoded the
    slider touched status into a direction enum. This struct can then be
    used via any of the USB interfaces to build a report as required,
    whether it be an analogue stick or trigger value.
    TODO: Clean up some of the previous state in the slider_read() function,
    it's somewhat confusing at the moment.
2026-01-28 Limit display refresh rate
    Using a temporary measure to try and limit how often the display is
    written to in order to minimise USB latency.
2026-01-28 Disable button debouncing
    Currently, the 3 count threshold for debouncing is too slow for it to
    process very fast button presses. Temporarily disabling the debouncing.
    I might look into rewriting how the debounce is handled in the future.
2026-02-19 First version enclosure design
    A laser cut enclosure intended to made with 6mm MDF. I have made some
    test pieces to work out tolerances for a laser kerf, but commit is a
    first version, prior to actually laser cutting an enclosure.
2026-02-20 Export enclosure panel laser cut drawings
